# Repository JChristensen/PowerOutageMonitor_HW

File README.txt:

README file for Arduino-Based Power Outage Logger board v1.2
https://github.com/JChristensen/PowerOutageMonitor_HW
Jack Christensen Dec 2021

This work is licensed under the Creative Commons Attribution-ShareAlike 4.0
International License. To view a copy of this license, visit
https://creativecommons.org/licenses/by-sa/4.0/ or send a letter to
Creative Commons, 171 Second Street, Suite 300, San Francisco, CA 94105, USA.

================================================================================
The version 1.2 board has updated routing which supports RTC 1Hz interrupt
without adding a wire.

An Arduino sketch for the board can be found at:
https://github.com/JChristensen/PowerOutageMonitor_SW

Boards can be ordered from OSH Park,
https://oshpark.com/shared_projects/b4qpXvHG

================================================================================
Assembly notes and options

1. The board is intended to be powered by either a 5V or a 7-12V AC adapter.
When using a 5V adapter, it MUST BE REGULATED; in this case, C1, C2, D1 and U2
do not need to be installed. Set the PWR SEL jumper (JP1) to DIRECT when using a
5V regulated adapter.

2. When disconnected from the power, certain 5V regulated adapters may emit a
power blip that the RTC interprets as a power-up event. This results in the
power-down and power-up timestamps being identical even if the power is left off
for several minutes. To eliminate this, power the RTC from an MCU pin by
selecting MCU power via the RTC PWR jumper (JP2). This is supported by the
sketch referenced above. It is also recommended to set the ATmega328P brown-out
detector to 4.3V by setting the extended fuse byte to 0x04. Note that when the
RTC is powered from the MCU pin, any MCU reset will cause a power outage to be
logged, whether or not it is associated with an actual power outage.

3. The Tinsharp TC1602A-09T 16x2 LCD display uses an LED backlight that requires
only 15mA at 5V. This means that a current-limiting resistor is not needed (use
a jumper in place of R5), and that the backlight can be powered from an MCU pin.
Do not use displays that require more than 20mA to operate the backlight. Note
also that some displays will require a non-zero value for R5 if their backlight
operates on less than 5V.

4. The board includes optional provisions for an on-board temperature sensor and
associated pullup resistor (U3, R6). An optional three-position terminal block
can also connect to an off-board sensor. The Arduino sketch referenced above
contains no code for these optional sensors.

5. Photocell PC1 is used to adjust the display backlight brightness to match the
ambient light level. The Arduino sketch above uses the internal AVR pullup
resistor in association with PC1, but if this does not result in satisfactory
adjustment of the backlight, then the internal pullup can be disabled and an
alternate resistor can be installed at R4.

================================================================================
Power Outage Logger Board
Bill of Materials

Part    Value               Device
C1      47uF                Radial lead electrolytic, 16V, 2 mm lead spacing
C2      100nF               50V MLCC, 0.1 in. lead spacing
C3      47uF                Radial lead electrolytic, 16V, 2 mm lead spacing
C4      100nF               50V MLCC, 0.1 in. lead spacing
C5      100nF               50V MLCC, 0.1 in. lead spacing
C6      100nF               50V MLCC, 0.1 in. lead spacing
C7      100nF               50V MLCC, 0.1 in. lead spacing
C8      27pF                50V MLCC, 0.1 in. lead spacing
C9      27pF                50V MLCC, 0.1 in. lead spacing
C10     100nF               50V MLCC, 0.1 in. lead spacing
D1      1N4004              Silicon rectifier
D2      1N4148              Signal diode
D3      5mm LED
J1      2.1mm power jack
JP1     Supply select       1x3 0.1 in. male header (or use jumper)
JP2     RTC power select    1x3 0.1 in. male header, right angle (or use jumper)
JP3     FTDI                1x6 0.1 in. male header, right angle
JP4     ICSP                2x3 0.1 in. male header (OPTIONAL)
PC1     CdS Photocell
PCB1    MCP79412            MCP79412 RTC Breakout Board, see:
                            https://github.com/JChristensen/rtc79412
PCB2    TC1602A-09T         Tinsharp 16x2 LCD
R1      10K                 1/8W 5% carbon film
R2      10K                 3/8 in. square trimpot, Bourns 3386P or equivalent
R3      330Ω                1/8W 5% carbon film
R4      10K                 1/8W 5% carbon film,
                            OPTIONAL pullup resistor for photocell (sketch uses
                            internal AVR pullup).
R5      0Ω                  1/8W 5% carbon film, current-limiting resistor for
                            LCD backlight.
                            Use a jumper with the TC1602A-09T display. Use
                            appropriate value for other displays.
R6      4.7K                1/8W 5% carbon film,
                            OPTIONAL pullup resistor for temperature/external
                            sensor.
S1      SET                 Omron B3F-312X
S2      UP                  Omron B3F-312X
S3      DN                  Omron B3F-312X
S4      RESET               Omron B3F-1020 (OPTIONAL)
TB1     Ext Sensor          3.5 mm x 3 terminal block, OST-TB-33.5MM or similar,
                            OPTIONAL for external sensor connection.
U1      ATmega328P-PU       Microcontroller
U2      78L05               5V 100mA Voltage Regulator
U3      DS18B20             Temperature Sensor (OPTIONAL)
Y1      16MHz               16MHz 18pF crystal

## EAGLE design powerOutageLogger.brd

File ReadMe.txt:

ReadMe file for Arduino-Based Power Outage Logger board v1.1
https://github.com/JChristensen/PowerOutageMonitor_HW
Jack Christensen Sep 2012

This work is licensed under the Creative Commons Attribution-ShareAlike 3.0
Unported License. To view a copy of this license, visit
http://creativecommons.org/licenses/by-sa/3.0/ or send a letter to Creative
Commons, 171 Second Street, Suite 300, San Francisco, California, 94105, USA.

================================================================================
This repository contains the following for the Power Outage Logger board:

Schematic
Eagle Files
Bill of materials (below)

An Arduino sketch for the board can be found at:
https://github.com/JChristensen/PowerOutageMonitor_SW

Boards can be ordered from OSH Park,
https://oshpark.com/shared_projects/5kJcAG7f

================================================================================
Assembly notes and options

1. The board is intended to be powered by either a 5V or a 7-12V AC adapter.
When using a 5V adapter, it MUST BE REGULATED; in this case, C1, C2, D1 and U2
do not need to be installed. Set the PWR SEL jumper (JP1) to DIRECT when using a
5V regulated adapter.

2. When disconnected from the power, certain 5V regulated adapters may emit a
power blip that the RTC interprets as a power-up event. This results in the
power-down and power-up timestamps being identical even if the power is left off
for several minutes. To eliminate this, power the RTC from an MCU pin by
selecting MCU power via the RTC PWR jumper (JP2). This is supported by the
sketch referenced above. It is also recommended to set the ATmega328P brown-out
detector to 4.3V by setting the extended fuse byte to 0x04. Note that when the
RTC is powered from the MCU pin, any MCU reset will cause a power outage to be
logged, whether or not it is associated with an actual power outage.

3. The Tinsharp TC1602A-09T 16x2 LCD display uses an LED backlight that requires
only 15mA at 5V. This means that a current-limiting resistor is not needed (use
a jumper in place of R5), and that the backlight can be powered from an MCU pin.
Do not use displays that require more than 20mA to operate the backlight. Note
also that some displays will require a non-zero value for R5 if their backlight
operates on less than 5V.

4. The board includes optional provisions for an on-board temperature sensor and
associated pullup resistor (U3, R6). An optional three-position terminal block
can also connect to an off-board sensor. The Arduino sketch referenced above
contains no code for these optional sensors.

5. Photocell PC1 is used to adjust the display backlight brightness to match the
ambient light level. The Arduino sketch above uses the internal AVR pullup
resistor in association with PC1, but if this does not result in satisfactory
adjustment of the backlight, then the internal pullup can be disabled and an
alternate resistor can be installed at R4.

================================================================================
Power Outage Logger Board
Bill of Materials

Part    Value               Device
C1      47uF                Radial lead electrolytic, 16V, 2 mm lead spacing
C2      100nF               50V MLCC, 0.1 in. lead spacing
C3      47uF                Radial lead electrolytic, 16V, 2 mm lead spacing
C4      100nF               50V MLCC, 0.1 in. lead spacing
C5      100nF               50V MLCC, 0.1 in. lead spacing
C6      100nF               50V MLCC, 0.1 in. lead spacing
C7      100nF               50V MLCC, 0.1 in. lead spacing
C8      27pF                50V MLCC, 0.1 in. lead spacing
C9      27pF                50V MLCC, 0.1 in. lead spacing
C10     100nF               50V MLCC, 0.1 in. lead spacing
D1      1N4004              Silicon rectifier
D2      1N4148              Signal diode
D3      5mm LED
J1      2.1mm power jack
JP1     Supply select       1x3 0.1 in. male header (or use jumper)
JP2     RTC power select    1x3 0.1 in. male header, right angle (or use jumper)
JP3     FTDI                1x6 0.1 in. male header, right angle
JP4     ICSP                2x3 0.1 in. male header (OPTIONAL)
PC1     CdS Photocell
PCB1    MCP79412            MCP79412 RTC Breakout Board, see:
                            https://github.com/JChristensen/rtc79412
PCB2    TC1602A-09T         Tinsharp 16x2 LCD
R1      10K                 1/8W 5% carbon film
R2      10K                 3/8 in. square trimpot, Bourns 3386P or equivalent
R3      330Ω                1/8W 5% carbon film
R4      10K                 1/8W 5% carbon film,
                            OPTIONAL pullup resistor for photocell (sketch uses
                            internal AVR pullup).
R5      0Ω                  1/8W 5% carbon film, current-limiting resistor for
                            LCD backlight.
                            Use a jumper with the TC1602A-09T display. Use
                            appropriate value for other displays.
R6      4.7K                1/8W 5% carbon film,
                            OPTIONAL pullup resistor for temperature/external
                            sensor.
S1      SET                 Omron B3F-312X
S2      UP                  Omron B3F-312X
S3      DN                  Omron B3F-312X
S4      RESET               Omron B3F-1020 (OPTIONAL)
TB1     Ext Sensor          3.5 mm x 3 terminal block, OST-TB-33.5MM or similar,
                            OPTIONAL for external sensor connection.
U1      ATmega328P-PU       Microcontroller
U2      78L05               5V 100mA Voltage Regulator
U3      DS18B20             Temperature Sensor (OPTIONAL)
Y1      16MHz               16MHz 18pF crystal

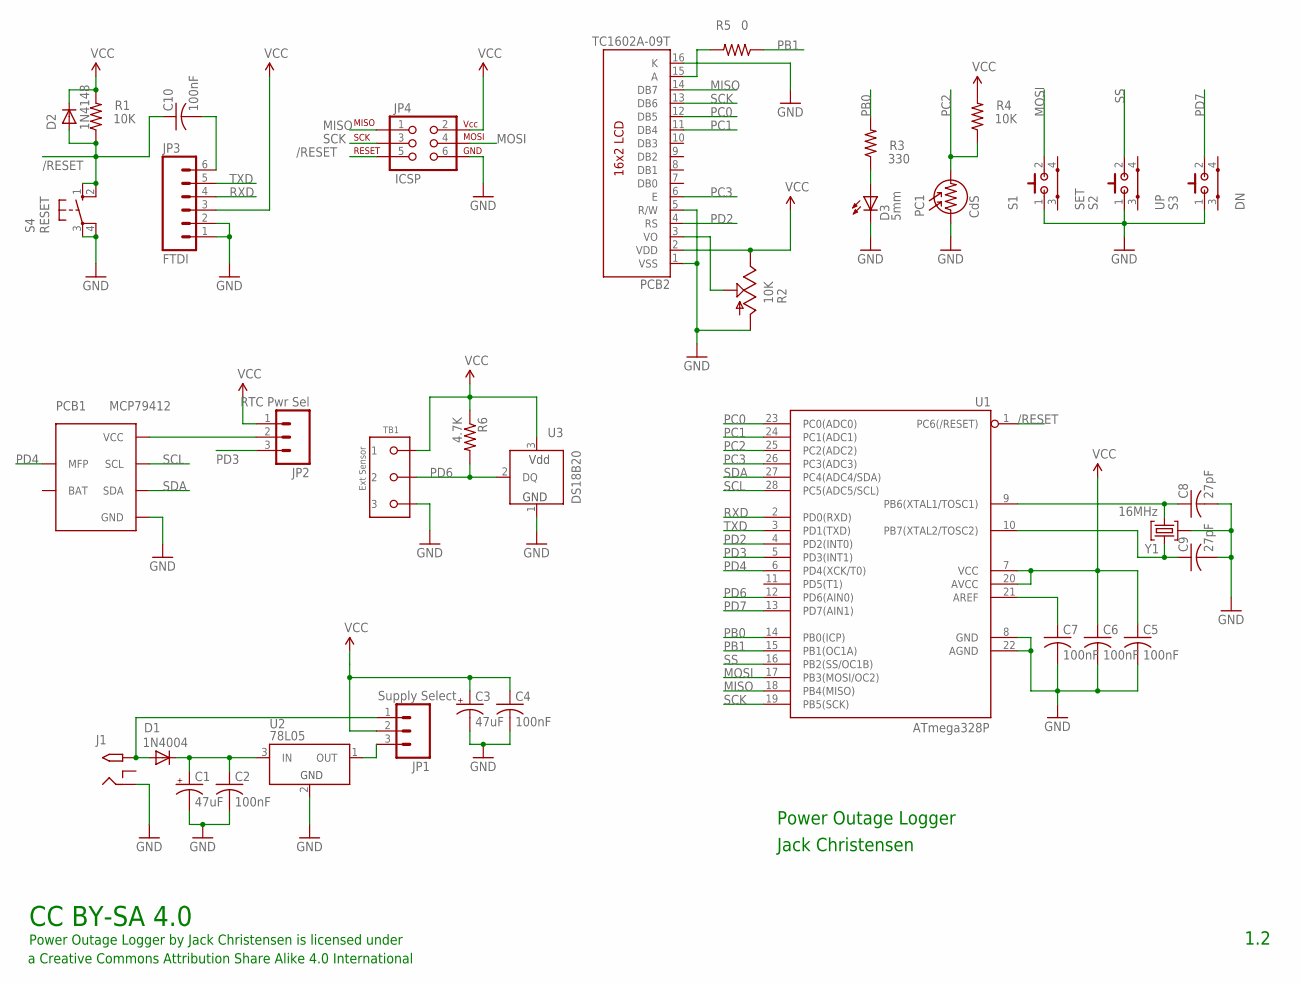
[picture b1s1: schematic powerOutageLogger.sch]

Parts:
C1, C3: 47uF; E2-5
C2, C4, C5, C6, C7, C10: 100nF; C025-025X050
C8, C9: 27pF; C025-025X050
D1: 1N4004; 1N400X
D2: 1N4148
D3: 5mm; LED5MM
J1: 2.1MMJACKTHM; PJ-102A
JP1: Supply Select; 1X03_LOCK
JP2: RTC Pwr Sel; 1X03_LOCK
JP3: FTDI; 1X06_LOCK
JP4: ICSP; 2X3
PC1: CdS; PHOTOCELL-020-017
PCB1: MCP79412; RTC79412
PCB2: TC1602A-09T; LCD-16X2
R1, R4: 10K; 0204/6
R2: 10K; TRIMPOT-3386P
R3: 330; 0204/6
R5: 0; 0204/6
R6: 4.7K; 0204/6
S1: SET; B3F-312X
S2: UP; B3F-312X
S3: DN; B3F-312X
S4: RESET; B3F-10XXOCT
TB1: Ext Sensor; OST-TB-3-3.5MM
U1: ATmega328P; DIL28-3
U2: 78L05; TO92-INLINE
U3: DS18B20; TO92-OVAL
Y1: 16MHz; RESONATOR

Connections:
/RESET: C10.1, D2.A, JP4.5, R1.1, S4.1 (S), S4.2 (S1), U1.1 (PC6(/RESET))
GND: C1.-, C2.2, C3.-, C4.2, C5.2, C6.2, C7.2, C8.2, C9.2, D3.K (C), J1.RING, JP3.1, JP3.2, JP4.6, PC1.P$1 (1), PCB1.8 (GND), PCB2.1 (VSS), PCB2.5 (R/W), PCB2.16 (K), R2.3 (A), S1.1, S2.1, S3.1, S4.3, S4.4 (P1), TB1.P$3 (3), U1.8 (GND), U1.22 (AGND), U2.2 (GND), U3.1 (GND), Y1.2
MISO: JP4.1, PCB2.14 (DB7), U1.18 (PB4(MISO))
MOSI: JP4.4, S1.2, U1.17 (PB3(MOSI/OC2))
unnamed: D1.A, J1.TIP, JP1.1
unnamed: C1.+, C2.1, D1.K, U2.3 (IN)
unnamed: PCB2.3 (VO), R2.2 (S)
unnamed: D3.A, R3.1
unnamed: JP2.2, PCB1.7 (VCC)
unnamed: PCB2.15 (A), R5.2
unnamed: C7.1, U1.21 (AREF)
OUT: JP1.3, U2.1 (OUT)
PB0: R3.2, U1.14 (PB0(ICP))
PB1: R5.1, U1.15 (PB1(OC1A))
PC0: PCB2.12 (DB5), U1.23 (PC0(ADC0))
PC1: PCB2.11 (DB4), U1.24 (PC1(ADC1))
PC2: PC1.P$2 (2), R4.1, U1.25 (PC2(ADC2))
PC3: PCB2.6 (E), U1.26 (PC3(ADC3))
PD2: PCB2.4 (RS), U1.4 (PD2(INT0))
PD3: JP2.3, U1.5 (PD3(INT1))
PD4: PCB1.3 (MFP), U1.6 (PD4(XCK/T0))
PD6: R6.2, TB1.P$2 (2), U1.12 (PD6(AIN0)), U3.2 (DQ)
PD7: S3.2, U1.13 (PD7(AIN1))
RST: C10.2, JP3.6
RXD: JP3.4, U1.2 (PD0(RXD))
SCK: JP4.3, PCB2.13 (DB6), U1.19 (PB5(SCK))
SCL: PCB1.6 (SCL), U1.28 (PC5(ADC5/SCL))
SDA: PCB1.5 (SDA), U1.27 (PC4(ADC4/SDA))
SS: S2.2, U1.16 (PB2(SS/OC1B))
TXD: JP3.5, U1.3 (PD1(TXD))
VCC: C3.+, C4.1, C5.1, C6.1, D2.K, JP1.2, JP2.1, JP3.3, JP4.2, PCB2.2 (VDD), R1.2, R2.1 (E), R4.2, R6.1, TB1.P$1 (1), U1.7 (VCC), U1.20 (AVCC), U3.3 (VDD)
XTAL1: C9.1, U1.10 (PB7(XTAL2/TOSC2)), Y1.1
XTAL2: C8.1, U1.9 (PB6(XTAL1/TOSC1)), Y1.3

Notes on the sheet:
Power Outage Logger by Jack Christensen is licensed under
CC BY-SA 4.0
a Creative Commons Attribution Share Alike 4.0 International
Power Outage Logger
Jack Christensen
1.2

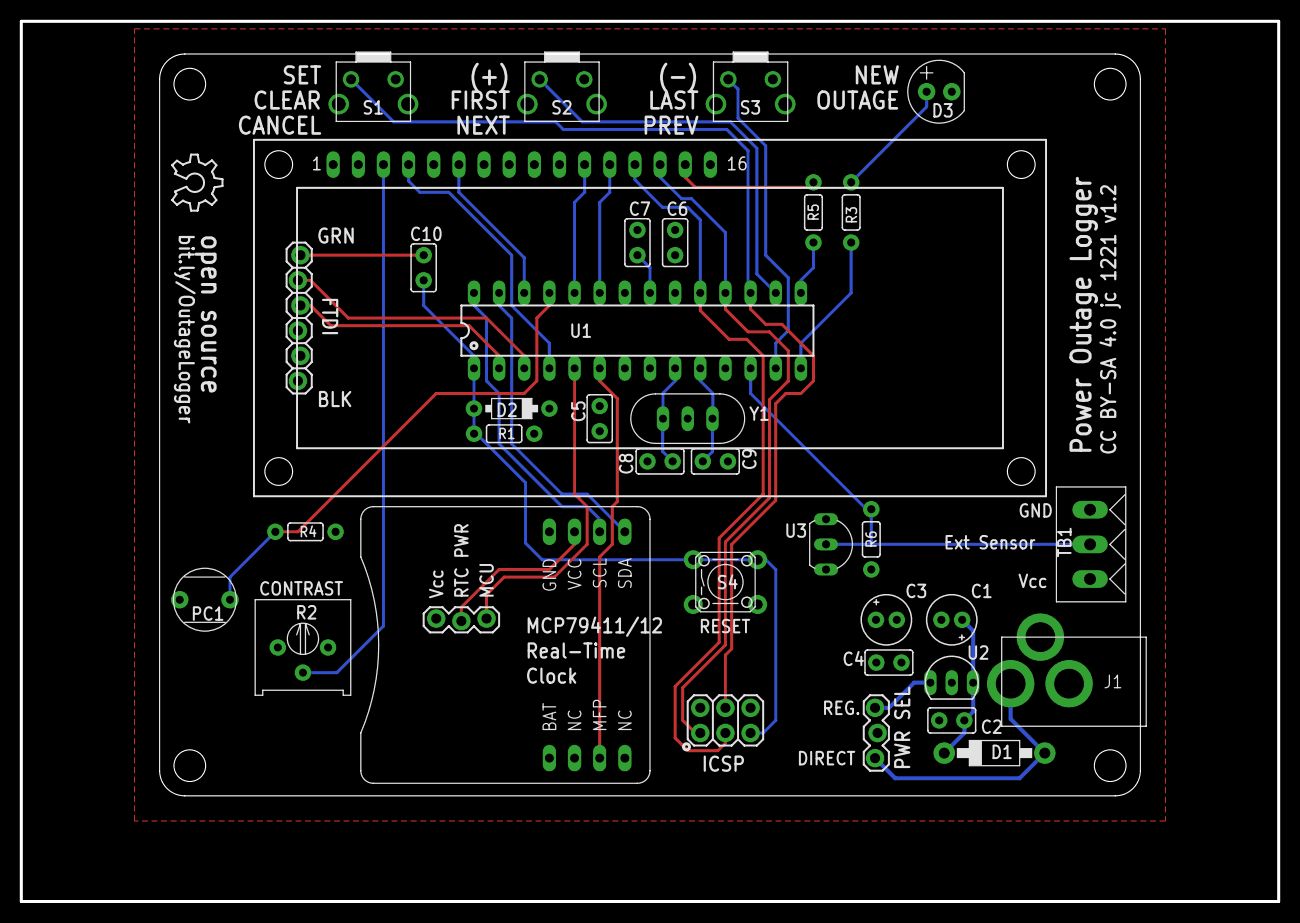
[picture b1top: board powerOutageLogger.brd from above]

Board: 2 copper layers, 127.0 x 88.9 mm, 38 parts (1 on the bottom side), 33 nets.

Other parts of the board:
U$1, U$2: OSHW_8X200_NOTEXT

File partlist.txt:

Partlist

Exported from powerOutageLogger.sch at 12/7/21 3:07 PM

EAGLE Version 9.6.2 Copyright (c) 1988-2020 Autodesk, Inc.

Assembly variant: 

Part     Value          Device             Package           Library  Sheet

C1       47uF           CPOL-USE2-5        E2-5              _jc      1
C2       100nF          C-US025-025X050    C025-025X050      _jc      1
C3       47uF           CPOL-USE2-5        E2-5              _jc      1
C4       100nF          C-US025-025X050    C025-025X050      _jc      1
C5       100nF          C-US025-025X050    C025-025X050      _jc      1
C6       100nF          C-US025-025X050    C025-025X050      _jc      1
C7       100nF          C-US025-025X050    C025-025X050      _jc      1
C8       27pF           C-US025-025X050    C025-025X050      _jc      1
C9       27pF           C-US025-025X050    C025-025X050      _jc      1
C10      100nF          C-US025-025X050    C025-025X050      _jc      1
D1       1N4004         DIODE1N400X        1N400X            _jc      1
D2       1N4148         DIODE1N4148        1N4148            _jc      1
D3       5mm            LED5MM             LED5MM            _jc      1
J1       2.1MMJACKTHM   2.1MMJACKTHM       PJ-102A           adafruit 1
JP1      Supply Select  M03LOCK            1X03_LOCK         SparkFun 1
JP2      RTC Pwr Sel    M03LOCK            1X03_LOCK         SparkFun 1
JP3      FTDI           M06LOCK            1X06_LOCK         SparkFun 1
JP4      ICSP           AVR_SPI_PRG_6PTH   2X3               _jc      1
PC1      CdS            PHOTOCELL020-017   PHOTOCELL-020-017 _jc      1
PCB1     MCP79412       RTC79412           RTC79412          _jc      1
PCB2     TC1602A-09T    LCD-16X2           LCD-16X2          SparkFun 1
R1       10K            R-US_0204/6        0204/6            _jc      1
R2       10K            TRIMPOT-3386P3386P TRIMPOT-3386P     _jc      1
R3       330            R-US_0204/6        0204/6            _jc      1
R4       10K            R-US_0204/6        0204/6            _jc      1
R5       0              R-US_0204/6        0204/6            _jc      1
R6       4.7K           R-US_0204/6        0204/6            _jc      1
S1       SET            B3F-312X           B3F-312X          _jc      1
S2       UP             B3F-312X           B3F-312X          _jc      1
S3       DN             B3F-312X           B3F-312X          _jc      1
S4       RESET          10-XXOCT           B3F-10XXOCT       _jc      1
TB1      Ext Sensor     OST-TB-33.5MM      OST-TB-3-3.5MM    _jc      1
U1       ATmega328P     AVR-MEGA8-PPTH     DIL28-3           SparkFun 1
U2       78L05          78XX-HTO92         TO92-INLINE       _jc      1
U3       DS18B20        DS18B20            TO92-OVAL         _jc      1
Y1       16MHz          RESONATOR          RESONATOR         _jc      1

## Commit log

2012-09-24 v1.0
2012-09-26 v1.1
2012-09-28 Version 1.1 Added ReadMe.txt Added schematic.png
2012-09-29 Fix typos in ReadMe.txt.
2012-10-03 Minor trace tweaks.
2012-10-04 Final layout as sent to fab.
2012-10-04 Add .gitignore file.
2012-11-07 ReadMe.txt minor changes
2012-11-07 Move labels on schematic for readability.
2014-02-14 Minor routing changes, fix hyperlinks in ReadMe.txt.
2021-12-07 Update for Eagle v9, Add gerbers.zip, board image, partlist.txt, Update ReadMe.
2021-12-07 Improved board routing, added connection for RTC interrupt.

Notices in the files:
powerOutageLogger.brd:
CC BY-SA 4.0 jc 1221 v1.2
parts and their libraries:
SparkFun: Licensing: CC v3.0 Share-Alike You are welcome to use this library for commercial purposes.
